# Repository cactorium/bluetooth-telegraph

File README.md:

# bluetooth-telegraph
(WIP) A Bluetooth keyboard that lets you tap your messages the old fashioned way

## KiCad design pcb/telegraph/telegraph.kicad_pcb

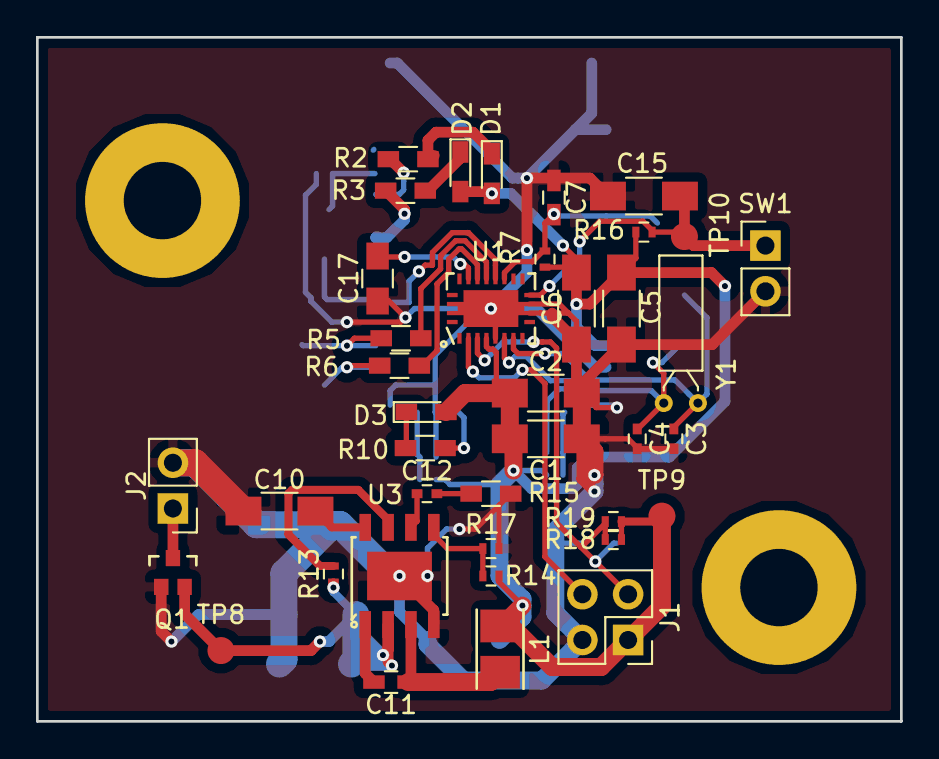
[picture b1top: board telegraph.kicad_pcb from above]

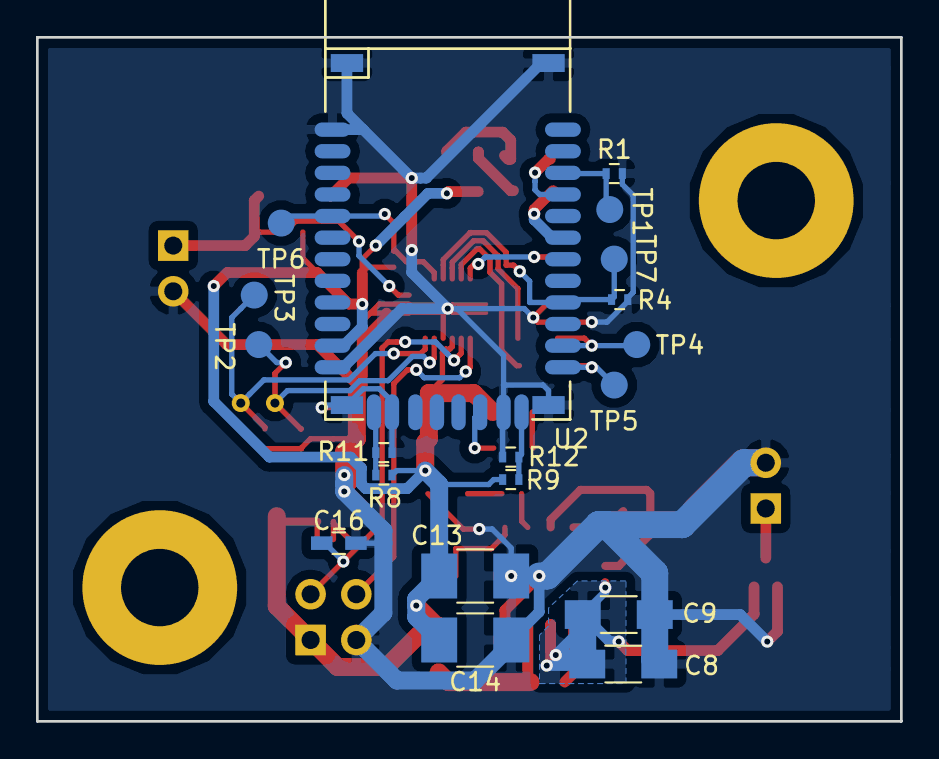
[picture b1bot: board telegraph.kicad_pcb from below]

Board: 2 copper layers, 48.0 x 38.0 mm, 60 parts (19 on the bottom side), 32 nets.

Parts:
C1: 10uF; C_1206_HandSoldering
C2, C5, C6, C10, C15: 100nF; C_1206_HandSoldering
C3, C4: 10pF; C_0402
C7, C11: 10nF; C_0603_HandSoldering
C8, C9: 10uF 16V; C_1206_HandSoldering
C12: 3.3nF; C_0402
C13, C14: 22uF; C_1210_HandSoldering
C16: 1nF; C_0603_HandSoldering
C17: 1uF; C_0805_HandSoldering
D1, D2, D3: LED_Small; LED_0603_HandSoldering
J1: Conn_02x02_Counter_Clockwise; Socket_Strip_Straight_2x02_Pitch2.54mm
J2: Conn_01x02; Socket_Strip_Straight_1x02_Pitch2.54mm
L1: 4.7uH; Inductor_Taiyo-Yuden_NR-24xx_HandSoldering
MH1, MH2: MountingHole; MountingHole_4.3mm_M4_Pad
Q1: RU1E002SPTCL; Rohm_UMT3F
R1, R4: 10k; R_0402
R2, R3, R5, R6, R10: 470; R_0603_HandSoldering
R7, R8, R9, R11, R12, R13, R16, R18, R19: 100k; R_0402
R14: 26.1k 1%; R_0402
R15: 13k; R_0603_HandSoldering
R17: 10k 1%; R_0402
SW1: SW_SPST; Socket_Strip_Straight_1x02_Pitch2.54mm
TP1, TP2, TP3, TP4, TP5, TP6, TP7, TP8, TP9, TP10: TestPoint; Measurement_Point_Round-SMD-Pad_Small
U1: MSP430FR2512IRHLR; TI_MSP430_QFN20
U2: RN42
U3: AP3513E; Diodes_SO8EP
Y1: 32.768kHz; Crystal_DS26_d2.0mm_l6.0mm_Horizontal

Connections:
/+3V3: C1.2, C2.1, C5.2, C6.2, C13.1, C14.1, D1.2, D2.2, D3.2, J1.1, L1.1, R7.1, R8.1, R9.1, R14.1, R16.1, R18.1, R19.1, TP9.1, U1.5, U2.11
/+VBAT: C8.2, C9.2, Q1.2, R13.1, TP8.1, U3.2
/AIO0: R9.2, R12.1, U2.30
/AIO1: R8.2, R11.1, U2.35
/MORSE: C15.1, R16.2, SW1.1, TP10.1, U1.11
/RN42_CTS: R4.1, TP7.1, U1.15, U2.16
/RN42_RSTN: C7.2, R7.2, TP6.1, U1.14, U2.5
/RN42_RX: R6.1, TP5.1, U2.13
/RN42_TX: R5.2, TP4.1, U2.14
/SBWTCK: J1.4, U1.3
/SWBTDIO: C16.1, J1.2, R18.2, R19.2, U1.4
GND: C1.1, C2.2, C3.2, C4.2, C5.1, C6.1, C7.1, C8.1, C9.1, C10.1, C13.2, C14.2, C15.2, C16.2, C17.2, J1.3, J2.2, Q1.1, R1.2, R4.2, R11.2, R12.2, R15.2, R17.2, SW1.2, U1.6, U1.21, U2.1, U2.12, U2.28, U2.29, U2.36, U3.4, U3.9
unnamed: C3.1, TP3.1, U1.8, Y1.1
unnamed: C4.1, TP2.1, U1.7, Y1.2
unnamed: C10.2, U3.8
unnamed: C11.1, L1.2, U3.3
unnamed: C11.2, U3.1
unnamed: C12.1, U3.6
unnamed: C12.2, R15.1
unnamed: C17.1, U1.18
unnamed: D1.1, R2.1
unnamed: D2.1, R3.1
unnamed: D3.1, R10.2
unnamed: J2.1, Q1.3
unnamed: R1.1, TP1.1, U2.22
unnamed: R2.2, U2.21
unnamed: R3.2, U2.19
unnamed: R5.1, U1.16
unnamed: R6.2, U1.17
unnamed: R10.1, U2.31
unnamed: R13.2, U3.7
unnamed: R14.2, R17.1, U3.5

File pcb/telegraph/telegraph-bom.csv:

Reference,Quantity,Identifier,Package,Value,Tolerance,Voltage,Current,Power,PN,Mouser
"U1","1","","","MSP430FR2512IRHLR","","","","","","595-430FR2512IRHLR"
"U2","1","","","RN42","","","","","","765-RN42HID-I/RM"
"U3","1","","","AP3513E","","","","","","621-AP3513EMPTR-G1"
"J1","1","","","Conn_02x02_Counter_Clockwise","","","","","","NoPart"
"C10;C6;C5;C2;C15","5","","","100nF","","","","","","77-VJ1206Y104KXXPBC"
"R13;R9;R12;R8;R11;R16;R18;R19;R7","9","","","100k","","","","","","755-SFR01MZPF1003"
"C12","1","","","3.3nF","","","","","","710-885012205047"
"R15","1","","","13k","","","","","","71-CRCW060313K0FKEAC"
"C11;C7","2","","","10nF","","","","","","77-VJ0603Y103KXAAC"
"C8;C9","2","","","10uF 16V","","","","","","74-TMCMA1C106MTRF"
"L1","1","","","4.7uH","","","","","","963-NRH2410T4R7MN"
"C14;C13","2","","","22uF","","","","","","581-TAJB226K016TNJ"
"R14","1","","","26.1k 1%","","","","","","652-CR0402-FX2612GLF"
"R17","1","","","10k 1%","","","","","","754-RR0510P-103D"
"TP1;TP4;TP5;TP8;TP9;TP6;TP7;TP10;TP2;TP3","10","","","TestPoint","","","","","","NoPart"
"D1;D3;D2","3","","","LED_Small","","","","","","710-150060VS75000"
"R2;R10;R3;R5;R6","5","","","470","","","","","","755-ESR03EZPJ471"
"J2","1","","","Conn_01x02","","","","","","NoPart"
"R4;R1","2","","","10k","","","","","","754-RR0510P-103D"
"C1","1","","","10uF","","","","","","74-TMCMA1C106MTRF"
"Y1","1","","","32.768kHz","","","","","","520-ECS327-6-13-X"
"C3;C4","2","","","10pF","","","","","","81-GRM0225C1C100JA3L"
"MH2;MH1","2","","","MountingHole","","","","","","NoPart"
"Q1","1","","","RU1E002SPTCL","","","","","","755-RU1E002SPTCL"
"SW1","1","","","SW_SPST","","","","","","NoPart"
"C16","1","","","1nF","","","","","","77-VJ0603Y102JXJPBC"
"C17","1","","","1uF","","","","","","603-CC805MKX7R6BB105"

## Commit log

2018-08-05 Initial schematic; TODO set all passive values
2018-08-06 Finished annotated schematic; TODO source and footprint
2018-08-07 Save before autofill
2018-08-07 Save before autofill; most parts sourced and autofill fixed
2018-08-07 Most parts sourced
2018-08-07 All components sourced
2018-08-08 Layout finished; need to move silkscreens around now
2018-08-08 Finish PCB board
2018-08-08 Replace RN42 RC pair with one easier to drive from MCU
2018-08-14 Try to fix Gerber from triggering short circuit warning
2018-08-16 Generate BOM
